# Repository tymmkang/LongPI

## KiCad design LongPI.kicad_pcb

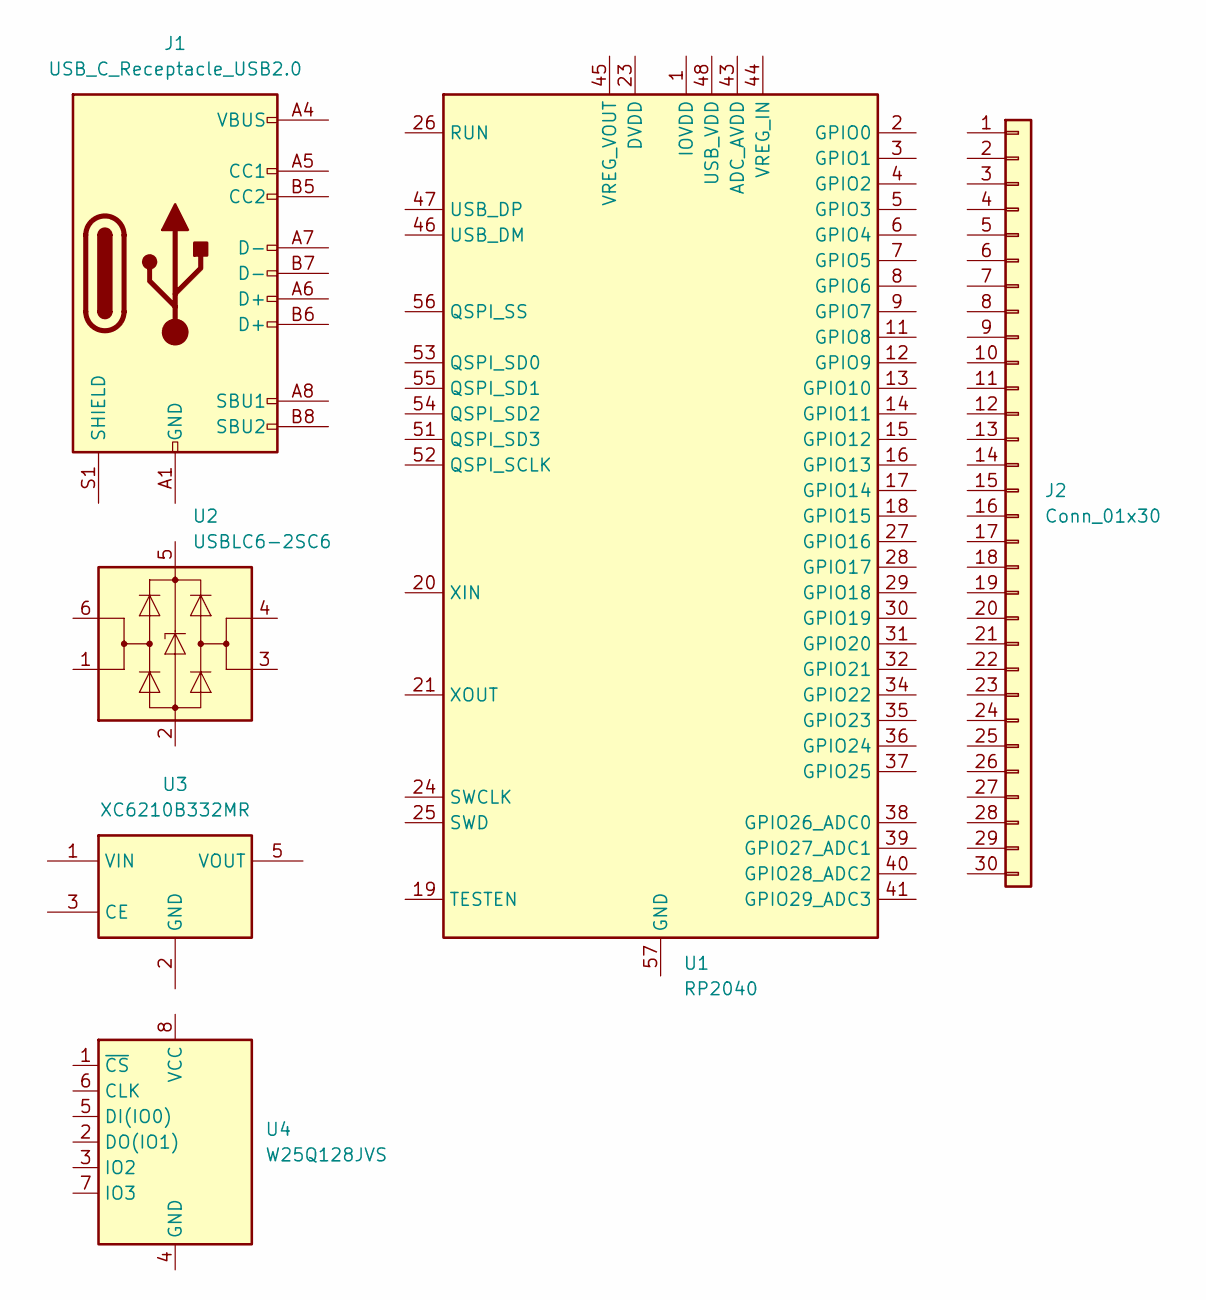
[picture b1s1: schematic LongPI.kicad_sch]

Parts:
J1: USB_C_Receptacle_USB2.0; USB_C_Receptacle_G-Switch_GT-USB-7010ASV
J2: Conn_01x30; PinHeader_2x30_P2.54mm_Vertical
U1: RP2040; QFN-56-1EP_7x7mm_P0.4mm_EP3.2x3.2mm
U2: USBLC6-2SC6; SOT-23-6
U3: XC6210B332MR; SOT-23-5
U4: W25Q128JVS; SOIC-8_5.23x5.23mm_P1.27mm

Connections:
unnamed: J1.A1 (GND), J1.A12 (GND), J1.B1 (GND), J1.B12 (GND)
unnamed: J1.A4 (VBUS), J1.A9 (VBUS), J1.B4 (VBUS), J1.B9 (VBUS)
unnamed: U1.23 (DVDD), U1.50 (DVDD)
unnamed: U1.1 (IOVDD), U1.10 (IOVDD), U1.22 (IOVDD), U1.33 (IOVDD), U1.42 (IOVDD), U1.49 (IOVDD)

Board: 2 copper layers, 6 parts (0 on the bottom side), 4 nets, no tracks yet.

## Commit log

2023-11-29 Add .gitignore
2023-11-29 Add KiCad project
2023-11-29 Add parts to sch, pcb
2023-12-16 USB-C setup on sch
2023-12-16 Voltage regulator setup on sch
2023-12-16 ESD protection setup on sch
2023-12-16 Flash setup on sch
2023-12-16 Crystal setup on sch
2023-12-24 Decoupling capacitors setup on sch
